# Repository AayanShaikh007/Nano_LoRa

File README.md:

# Nano LoRa - RP2350 Based Development Board

Almost done! will upload files in a few days

This PCB design is licensed under CC BY-NC 4.0 — free to use and modify for non-commercial purposes only.

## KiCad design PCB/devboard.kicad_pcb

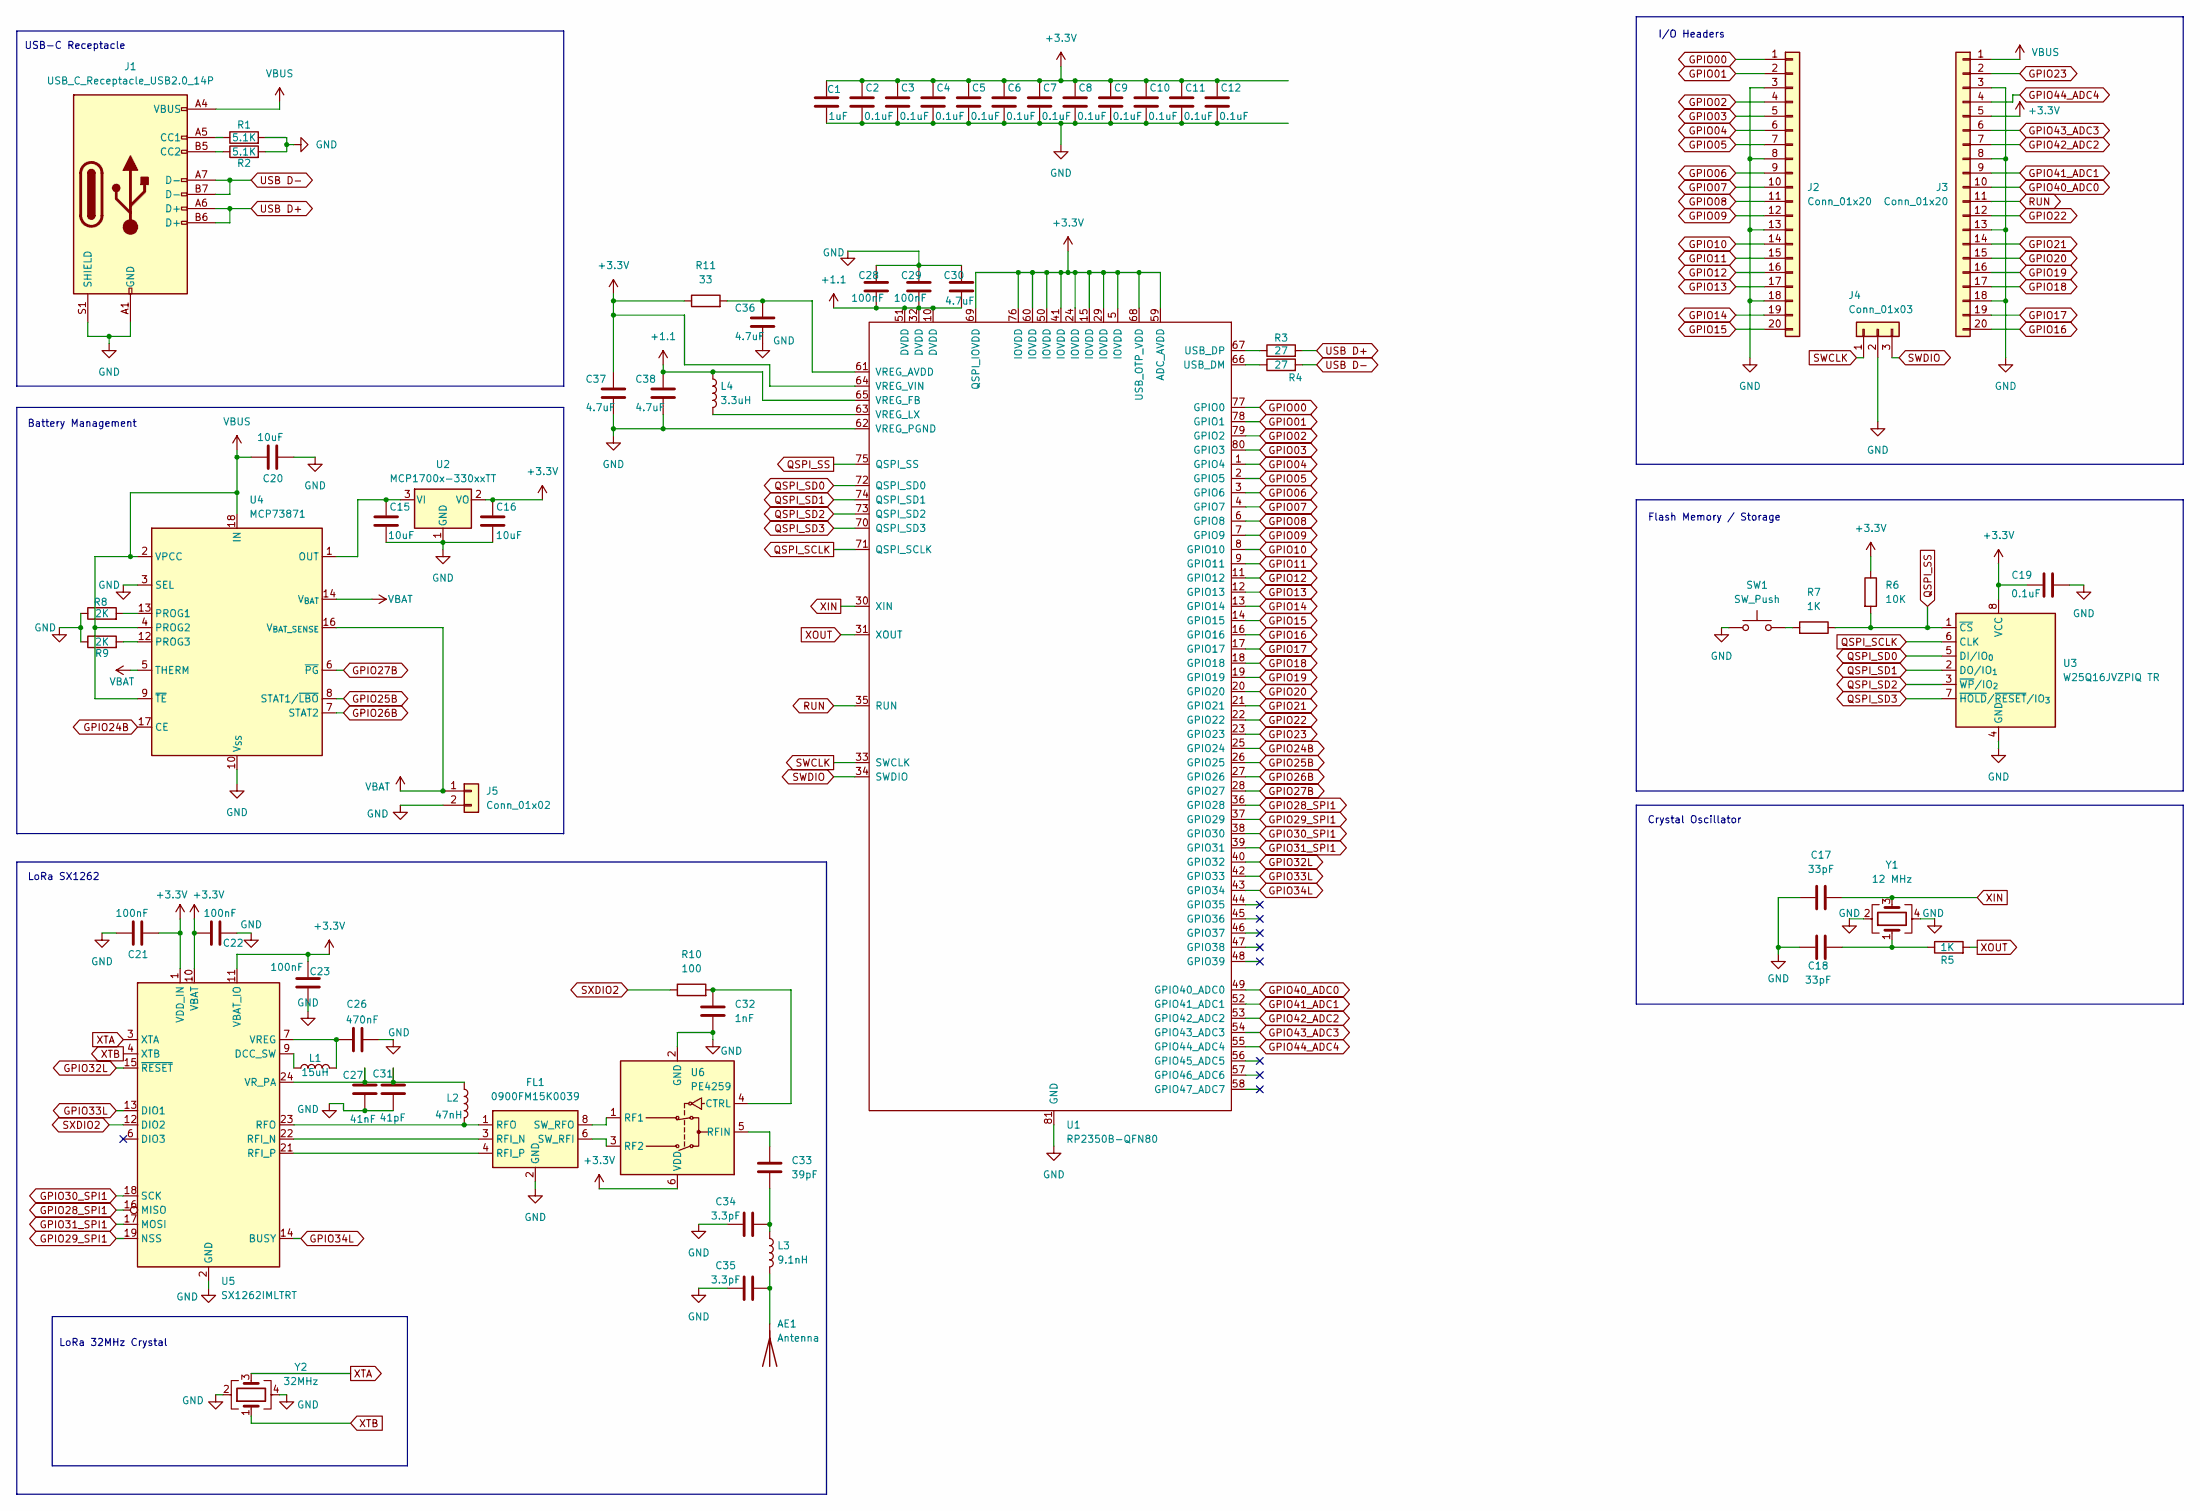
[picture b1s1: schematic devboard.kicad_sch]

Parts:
AE1: Antenna; PinSocket_1x01_P2.54mm_Vertical
C1: 1uF; C_0402_1005Metric
C2, C3, C4, C5, C6, C7, C8, C9, C10, C11, C12, C19: 0.1uF; C_0402_1005Metric
C15, C16, C20: 10uF; C_0603_1608Metric
C17, C18: 33pF; C_0201_0603Metric
C21, C22, C23, C28, C29: 100nF; C_0402_1005Metric
C26: 470nF; C_0402_1005Metric
C27: 41nF; C_0402_1005Metric
C30: 4.7uF; C_0201_0603Metric
C31: 41pF; C_0402_1005Metric
C32: 1nF; C_0402_1005Metric
C33: 39pF; C_0402_1005Metric
C34, C35: 3.3pF; C_0402_1005Metric
C36, C37, C38: 4.7uF; C_0402_1005Metric
FL1: 0900FM15K0039; Balun_Johanson_0900FM15K0039
J1: USB_C_Receptacle_USB2.0_14P; USB_C_Receptacle_HRO_TYPE-C-31-M-12
J2, J3: Conn_01x20; PinHeader_1x20_P2.54mm_Vertical
J4: Conn_01x03; PinHeader_1x03_P2.54mm_Vertical
J5: Conn_01x02; Molex_PicoBlade_53047-0210_1x02_P1.25mm_Vertical
L1: 15uH; L_0402_1005Metric
L2: 47nH; L_0402_1005Metric
L3: 9.1nH; L_0402_1005Metric
L4: 3.3uH; L_0402_1005Metric
R1, R2: 5.1K; R_0402_1005Metric
R3, R4: 27; R_0402_1005Metric
R5, R7: 1K; R_0402_1005Metric
R6: 10K; R_0402_1005Metric
R8, R9: 2K; R_0402_1005Metric
R10: 100; R_0402_1005Metric
R11: 33; R_0402_1005Metric
SW1: SW_Push; SW_Push_SPST_NO_Alps_SKRK
U1: RP2350B-QFN80; QFN-80-1EP_10x10mm_P0.4mm_EP3.4x3.4mm
U2: MCP1700x-330xxTT; SOT-23
U3: W25Q16JVZPIQ TR; Winbond_USON-8-1EP_3x2mm_P0.5mm_EP0.2x1.6mm
U4: MCP73871; QFN-20-1EP_4x4mm_P0.5mm_EP2.5x2.5mm
U5: SX1262IMLTRT; QFN-24-1EP_4x4mm_P0.5mm_EP2.6x2.6mm
U6: PE4259; SOT-363_SC-70-6
Y1: 12 MHz; Crystal_SMD_3225-4Pin_3.2x2.5mm
Y2: 32MHz; Crystal_SMD_3225-4Pin_3.2x2.5mm

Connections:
+1.1: C28.2, C29.2, C30.2, C38.1, L4.1, U1.10 (DVDD), U1.32 (DVDD), U1.51 (DVDD), U1.65 (VREG_FB)
+3.3V: C1.1, C2.1, C3.1, C4.1, C5.1, C6.1, C7.1, C8.1, C9.1, C10.1, C11.1, C12.1, C16.1, C19.1, C21.2, C22.1, C23.2, C37.1, J3.5, R6.1, R11.1, U1.5 (IOVDD), U1.15 (IOVDD), U1.24 (IOVDD), U1.29 (IOVDD), U1.41 (IOVDD), U1.50 (IOVDD), U1.59 (ADC_AVDD), U1.60 (IOVDD), U1.64 (VREG_VIN), U1.68 (USB_OTP_VDD), U1.69 (QSPI_IOVDD), U1.76 (IOVDD), U2.2 (VO), U3.8 (VCC), U5.1 (VDD_IN), U5.10 (VBAT), U5.11 (VBAT_IO), U6.6 (VDD)
GND: C1.2, C2.2, C3.2, C4.2, C5.2, C6.2, C7.2, C8.2, C9.2, C10.2, C11.2, C12.2, C15.2, C16.2, C17.1, C18.1, C19.2, C20.2, C21.1, C22.2, C23.1, C26.2, C27.2, C28.1, C29.1, C30.1, C31.2, C32.2, C34.1, C35.1, C36.2, C37.2, C38.2, FL1.2 (GND), FL1.5 (GND), FL1.7 (GND), FL1.9 (GND), FL1.10 (GND), J1.A1 (GND), J1.A12 (GND), J1.B1 (GND), J1.B12 (GND), J1.S1 (SHIELD), J2.3, J2.8, J2.13, J2.18, J3.3, J3.8, J3.13, J3.18, J4.2, J5.2, R1.2, R2.2, R8.1, R9.1, SW1.1, U1.62 (VREG_PGND), U1.81 (GND), U2.1 (GND), U3.4 (GND), U4.3 (SEL), U4.10 (V_{SS}), U4.11 (V_{SS}), U4.21 (V_{SS}), U5.2 (GND), U5.5 (GND), U5.8 (GND), U5.20 (GND), U5.25 (GND), U6.2 (GND), Y1.2, Y1.4, Y2.2, Y2.4
GPIO00: J2.1, U1.77 (GPIO0)
GPIO01: J2.2, U1.78 (GPIO1)
GPIO02: J2.4, U1.79 (GPIO2)
GPIO03: J2.5, U1.80 (GPIO3)
GPIO04: J2.6, U1.1 (GPIO4)
GPIO05: J2.7, U1.2 (GPIO5)
GPIO06: J2.9, U1.3 (GPIO6)
GPIO07: J2.10, U1.4 (GPIO7)
GPIO08: J2.11, U1.6 (GPIO8)
GPIO09: J2.12, U1.7 (GPIO9)
GPIO10: J2.14, U1.8 (GPIO10)
GPIO11: J2.15, U1.9 (GPIO11)
GPIO12: J2.16, U1.11 (GPIO12)
GPIO13: J2.17, U1.12 (GPIO13)
GPIO14: J2.19, U1.13 (GPIO14)
GPIO15: J2.20, U1.14 (GPIO15)
GPIO16: J3.20, U1.16 (GPIO16)
GPIO17: J3.19, U1.17 (GPIO17)
GPIO18: J3.17, U1.18 (GPIO18)
GPIO19: J3.16, U1.19 (GPIO19)
GPIO20: J3.15, U1.20 (GPIO20)
GPIO21: J3.14, U1.21 (GPIO21)
GPIO22: J3.12, U1.22 (GPIO22)
GPIO23: J3.2, U1.23 (GPIO23)
GPIO24B: U1.25 (GPIO24), U4.17 (CE)
GPIO25B: U1.26 (GPIO25), U4.8 (STAT1/~LBO)
GPIO26B: U1.27 (GPIO26), U4.7 (STAT2)
GPIO27B: U1.28 (GPIO27), U4.6 (~PG)
GPIO28_SPI1: U1.36 (GPIO28), U5.16 (MISO)
GPIO29_SPI1: U1.37 (GPIO29), U5.19 (NSS)
GPIO30_SPI1: U1.38 (GPIO30), U5.18 (SCK)
GPIO31_SPI1: U1.39 (GPIO31), U5.17 (MOSI)
GPIO32L: U1.40 (GPIO32), U5.15 (~RESET)
GPIO33L: U1.42 (GPIO33), U5.13 (DIO1)
GPIO34L: U1.43 (GPIO34), U5.14 (BUSY)
GPIO40_ADC0: J3.10, U1.49 (GPIO40_ADC0)
GPIO41_ADC1: J3.9, U1.52 (GPIO41_ADC1)
GPIO42_ADC2: J3.7, U1.53 (GPIO42_ADC2)
GPIO43_ADC3: J3.6, U1.54 (GPIO43_ADC3)
GPIO44_ADC4: J3.4, U1.55 (GPIO44_ADC4)
unnamed: AE1.1 (A), C35.2, L3.2
unnamed: C18.2, R5.1, Y1.1
unnamed: C33.2, C34.2, L3.1
unnamed: FL1.3 (RFI_N), U5.22 (RFI_N)
unnamed: FL1.4 (RFI_P), U5.21 (RFI_P)
unnamed: FL1.1 (RFO), L2.2, U5.23 (RFO)
unnamed: FL1.6 (SW_RFI), U6.3 (RF2)
unnamed: FL1.8 (SW_RFO), U6.1 (RF1)
unnamed: J1.A5 (CC1), R1.1
unnamed: J1.B5 (CC2), R2.1
unnamed: R7.2, SW1.2
unnamed: R4.1, U1.66 (USB_DM)
unnamed: R3.1, U1.67 (USB_DP)
unnamed: C36.1, R11.2, U1.61 (VREG_AVDD)
unnamed: L4.2, U1.63 (VREG_LX)
unnamed: C15.1, U2.3 (VI), U4.1 (OUT), U4.20 (OUT)
unnamed: R8.2, U4.13 (PROG1)
unnamed: R9.2, U4.12 (PROG3)
unnamed: L1.1, U5.9 (DCC_SW)
unnamed: C26.1, L1.2, U5.7 (VREG)
unnamed: C27.1, C31.1, L2.1, U5.24 (VR_PA)
unnamed: C32.1, R10.2, U6.4 (CTRL)
unnamed: C33.1, U6.5 (RFIN)
QSPI_SCLK: U1.71 (QSPI_SCLK), U3.6 (CLK)
QSPI_SD0: U1.72 (QSPI_SD0), U3.5 (DI/IO_{0})
QSPI_SD1: U1.74 (QSPI_SD1), U3.2 (DO/IO_{1})
QSPI_SD2: U1.73 (QSPI_SD2), U3.3 (~WP/IO_{2})
QSPI_SD3: U1.70 (QSPI_SD3), U3.7 (~HOLD/~RESET/IO_{3})
QSPI_SS: R6.2, R7.1, U1.75 (QSPI_SS), U3.1 (~CS)
RUN: J3.11, U1.35 (RUN)
SWCLK: J4.1, U1.33 (SWCLK)
SWDIO: J4.3, U1.34 (SWDIO)
SXDIO2: R10.1, U5.12 (DIO2)
USB D+: J1.A6 (D+), J1.B6 (D+), R3.2
USB D-: J1.A7 (D-), J1.B7 (D-), R4.2
VBAT: J5.1, U4.5 (THERM), U4.14 (V_{BAT}), U4.15 (V_{BAT}), U4.16 (V_{BAT_SENSE})
VBUS: C20.1, J1.A4 (VBUS), J1.A9 (VBUS), J1.B4 (VBUS), J1.B9 (VBUS), J3.1, U4.2 (VPCC), U4.4 (PROG2), U4.9 (~TE), U4.18 (IN), U4.19 (IN)
XIN: C17.2, U1.30 (XIN), Y1.3
XOUT: R5.2, U1.31 (XOUT)
XTA: U5.3 (XTA), Y2.3
XTB: U5.4 (XTB), Y2.1

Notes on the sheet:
LoRa SX1262
I/O Headers
Battery Management
Flash Memory / Storage
Crystal Oscillator
LoRa 32MHz Crystal
USB-C Receptacle

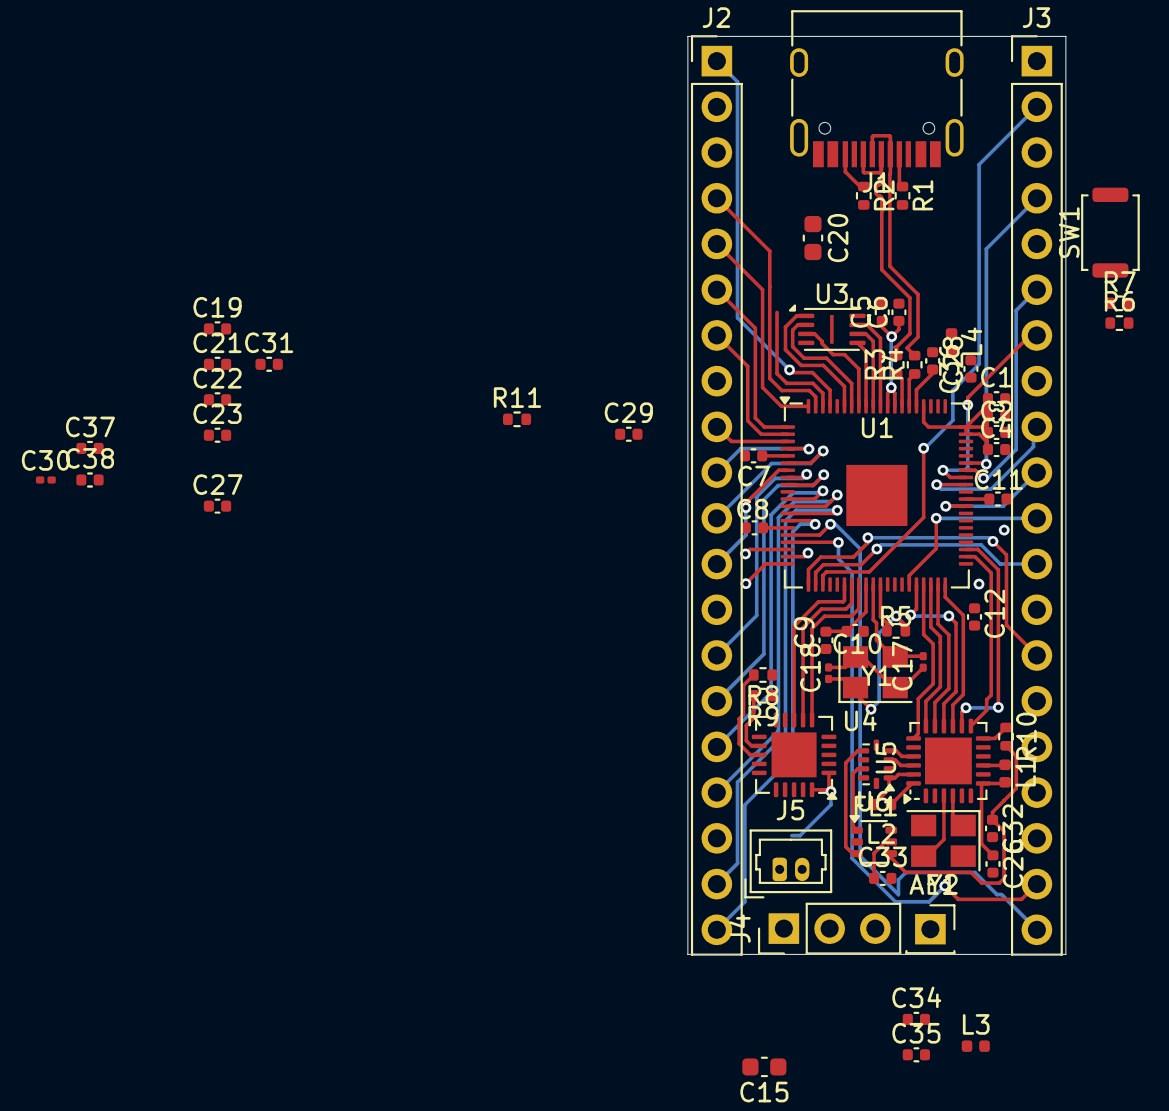
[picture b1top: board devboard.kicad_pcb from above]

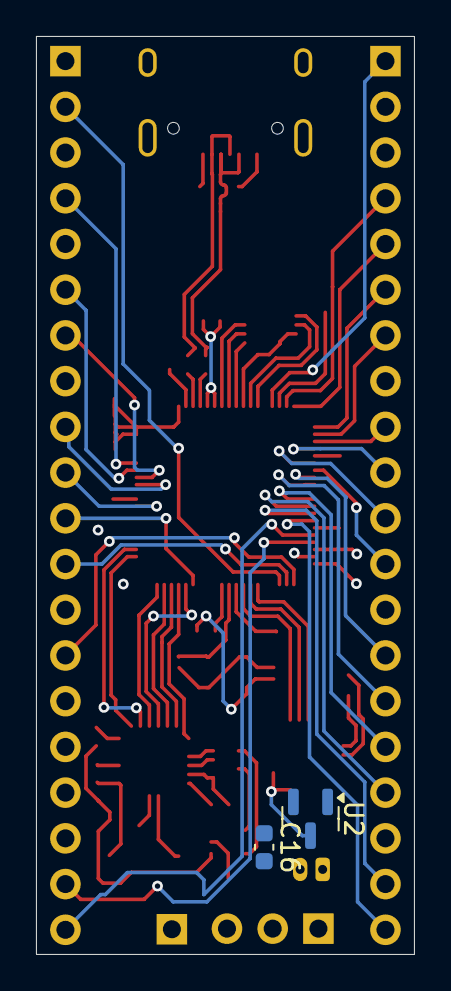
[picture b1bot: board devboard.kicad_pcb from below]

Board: 4 copper layers, 21.0 x 51.0 mm, 65 parts (2 on the bottom side), 84 nets.

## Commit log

2026-01-08 Create README for Nano LoRa development board
    Added initial README content for Nano LoRa project.
2026-01-12 pcb files
2026-01-12 Add LICENSE file for CC BY-NC 4.0
    Added a Creative Commons Attribution-NonCommercial 4.0 license file.
2026-01-12 Include licensing details in README
    Added licensing information for PCB design.
